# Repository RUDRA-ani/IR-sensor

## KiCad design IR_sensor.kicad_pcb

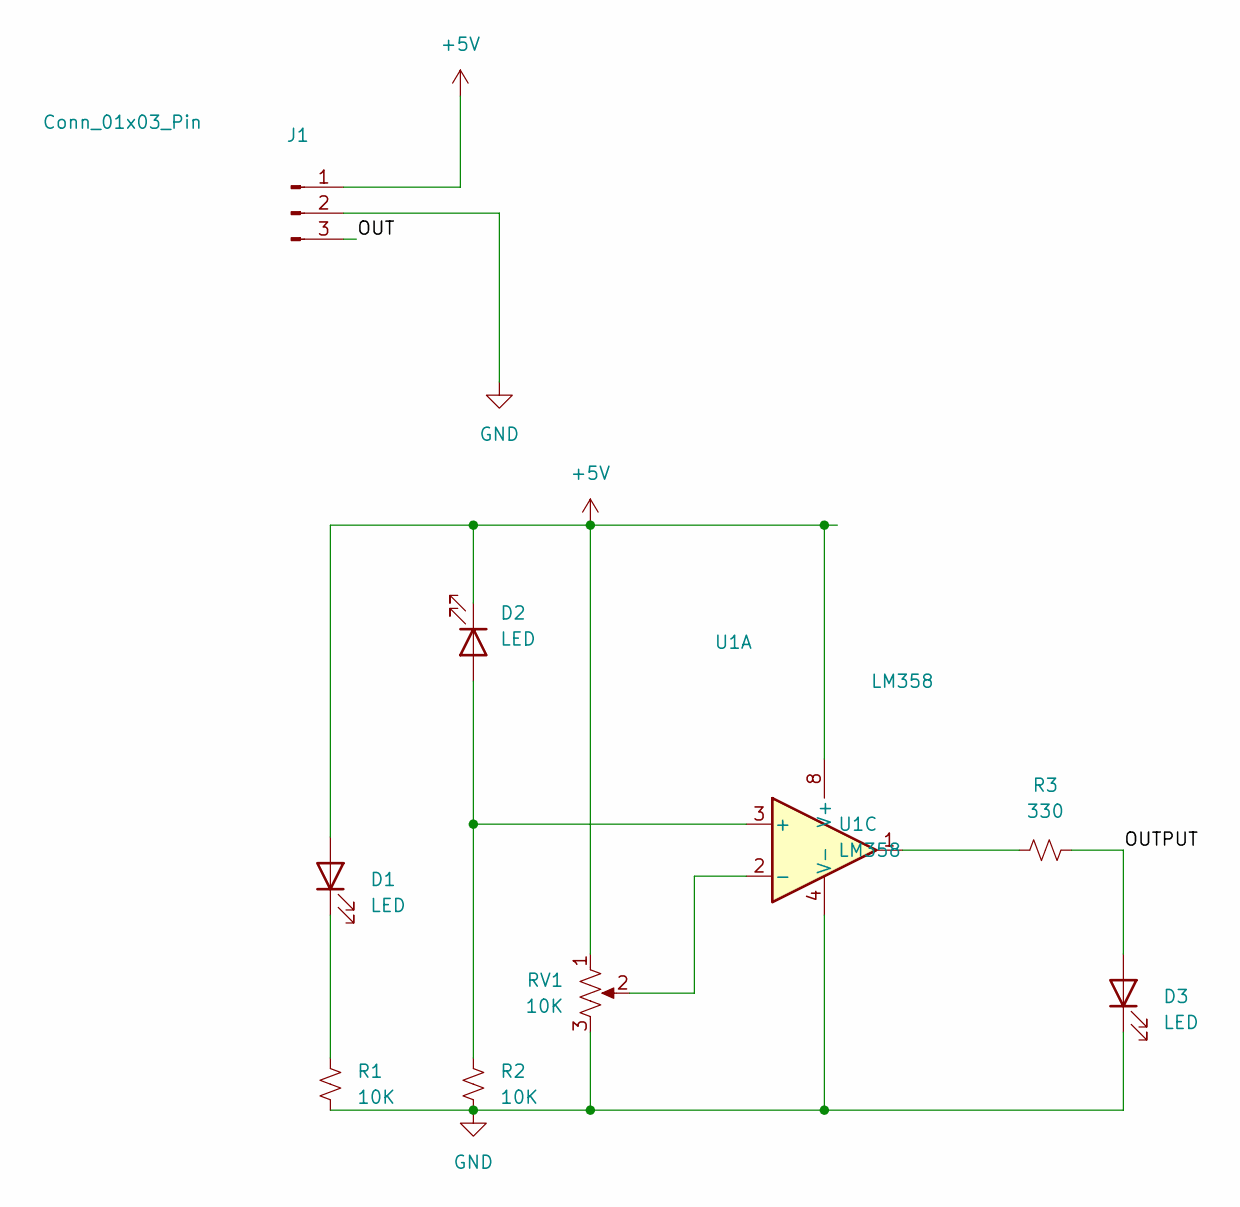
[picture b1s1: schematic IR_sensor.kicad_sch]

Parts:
D1, D2: LED; LED_D5.0mm_Horizontal_O3.81mm_Z3.0mm
D3: LED; LED_1206_3216Metric_Pad1.42x1.75mm_HandSolder
J1: Conn_01x03_Pin; PinHeader_1x03_P2.54mm_Horizontal
R1, R2: 10K; R_1206_3216Metric_Pad1.30x1.75mm_HandSolder
R3: 330; R_1206_3216Metric_Pad1.30x1.75mm_HandSolder
RV1: 10K; Potentiometer_Bourns_3266Z_Horizontal
U1: LM358; DIP-8_W7.62mm_SMDSocket_SmallPads

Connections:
+5V: D1.2 (A), D2.1 (K), J1.1, RV1.1, U1.8 (V+)
/OUT: J1.3
/OUTPUT: D3.2 (A), R3.2
GND: D3.1 (K), J1.2, R1.1, R2.1, RV1.3, U1.4 (V-)
unnamed: D1.1 (K), R1.2
unnamed: D2.2 (A), R2.2, U1.3 (+)
unnamed: R3.1, U1.1
unnamed: RV1.2, U1.2 (-)

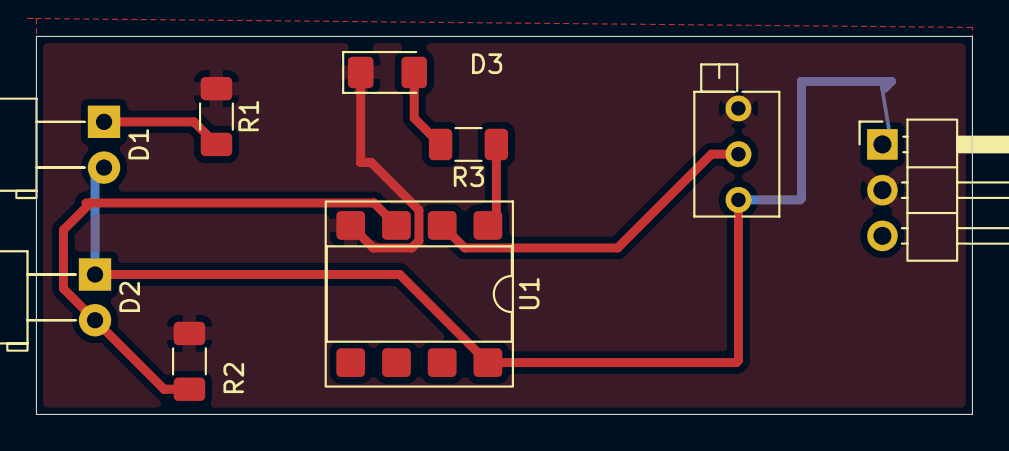
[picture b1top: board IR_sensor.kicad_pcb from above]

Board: 2 copper layers, 52.0 x 21.0 mm, 9 parts (0 on the bottom side), 7 nets.
